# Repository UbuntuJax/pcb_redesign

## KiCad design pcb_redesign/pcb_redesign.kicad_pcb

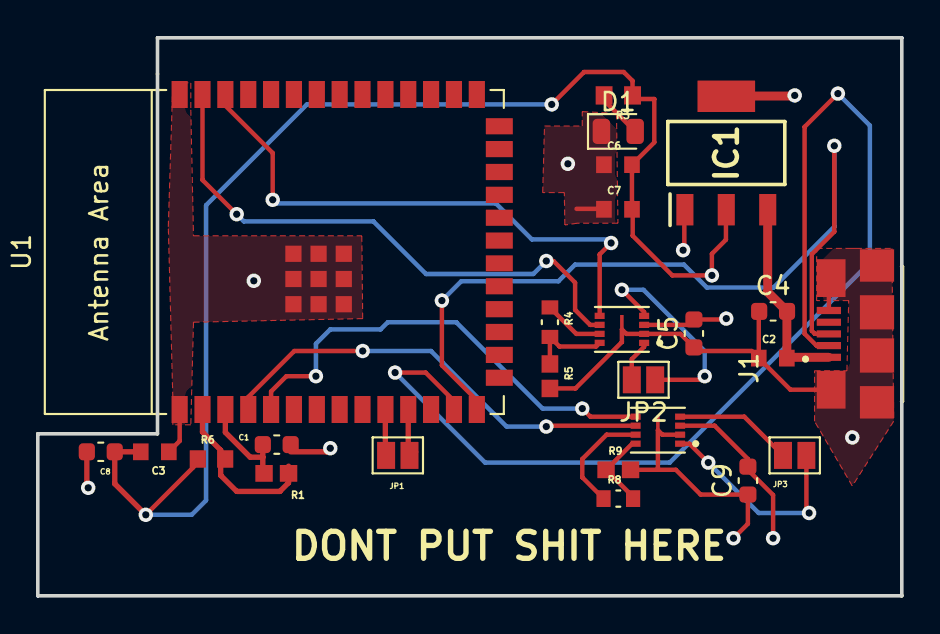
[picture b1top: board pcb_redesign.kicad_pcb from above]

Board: 4 copper layers, 48.0 x 31.0 mm, 25 parts (0 on the bottom side), 22 nets.

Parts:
A3908EEETR-T1, A3908EEETR-T3: PSON50P200X300X60-9N
C1: 1uF/16V(10%); C_0603_1608Metric
C2, C7: 10uF; CAPC1608X90N
C3: 10uF/6.7V (10%); CAPC1608X90N
C4: 0.1uF; C_0603_1608Metric
C5, C9: 10uF; C_0603_1608Metric
C6: 0.1uF; CAPC1608X90N
C8: 0.1uF/50V(10%); C_0603_1608Metric
D1: LED; LED_0805_2012Metric
IC1: SPX1117M3-L-3-3_TR; SOT230P700X180-4N
J1: USB_B_Micro; AMPHENOL_10118192-0002LF
JP1, JP2, JP3: SolderJumper_2_Open; SolderJumper-2_P1.3mm_Open_Pad1.0x1.5mm
R1: 10K(1%); RESC1508X50N
R3: 100 ohm; RESC1608X50N
R4, R8: 10k; RESC1608X55N
R5, R9: 30k; RESC1508X50N
R6: 0(1%); RESC1508X55N
U1: ESP32-S3-WROOM-1

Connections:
3.7_UNREG: C2.2, C4.2, IC1.3 (VIN), J1.1 (VBUS)
/CHIP_PU: C1.1, R1.2, U1.3 (EN)
/ESP32_3V3: R1.1, R6.2, U1.2 (3V3)
D+: J1.3 (D+), U1.14 (GPIO20/U1CTS/ADC2_CH9/CLK_OUT1/USB_D+)
D-: J1.2 (D-), U1.13 (GPIO19/U1RTS/ADC2_CH8/CLK_OUT2/USB_D-)
ENA Left Motor: A3908EEETR-T1.6 (IN_1), U1.39 (GPIO1/TOUCH1/ADC1_CH0)
ENA Right Motor: A3908EEETR-T3.5 (IN_2), U1.5 (GPIO5/TOUCH5/ADC1_CH4)
ENB Left Motor: A3908EEETR-T1.5 (IN_2), U1.38 (GPIO2/TOUCH2/ADC1_CH1)
ENB Right Motor: A3908EEETR-T3.6 (IN_1), U1.4 (GPIO4/TOUCH4/ADC1_CH3)
GND: A3908EEETR-T1.2 (GND), A3908EEETR-T1.9 (EP), A3908EEETR-T3.2 (GND), A3908EEETR-T3.9 (EP), C1.2, C2.1, C3.1, C4.1, C5.1, C6.1, C7.1, C8.1, C9.1, D1.1 (K), IC1.1 (ADJ/GND), J1.5 (GND), J1.S1 (in1), J1.S2 (in2), J1.S3 (in3), J1.S4 (in4), J1.S5 (in5), J1.S6 (in6), R5.2, R9.2, U1.1 (GND), U1.40 (GND), U1.41 (GND)
unnamed: A3908EEETR-T1.4 (OUTA), JP2.1 (A)
unnamed: A3908EEETR-T1.1 (OUTB), JP2.2 (B)
unnamed: A3908EEETR-T1.7 (VREF), R4.1
unnamed: A3908EEETR-T1.8 (VSET), R4.2, R5.1
unnamed: A3908EEETR-T3.4 (OUTA), JP3.1 (A)
unnamed: A3908EEETR-T3.1 (OUTB), JP3.2 (B)
unnamed: A3908EEETR-T3.7 (VREF), R8.1
unnamed: A3908EEETR-T3.8 (VSET), R8.2, R9.1
unnamed: D1.2 (A), R3.2
unnamed: JP1.1 (A), U1.11 (GPIO18/U1RXD/ADC2_CH7/CLK_OUT3)
unnamed: JP1.2 (B), U1.10 (GPIO17/U1TXD/ADC2_CH6)
VCC_3V3: A3908EEETR-T1.3 (VDD), A3908EEETR-T3.3 (VDD), C3.2, C5.2, C6.2, C7.2, C8.2, C9.2, IC1.2 (VOUT_1), IC1.4 (VOUT_2), R3.1, R6.1

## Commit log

2023-05-11 12.21 may 11
2023-05-11 Finished 1st draft of schematic
2023-05-11 5.55pm 11.05
2023-05-11 schematic imported
2023-05-11 added outline in pcb editor
2023-05-12 components added to board
2023-05-12 switching to laptop
2023-05-12 added layers and filled the board
2023-05-12 wired up 2.13
2023-05-12 getting lunch
2023-05-12 finished design
2023-05-13 finished adding decoupling caps, shipped off to jlc
2023-05-13 user/pass
